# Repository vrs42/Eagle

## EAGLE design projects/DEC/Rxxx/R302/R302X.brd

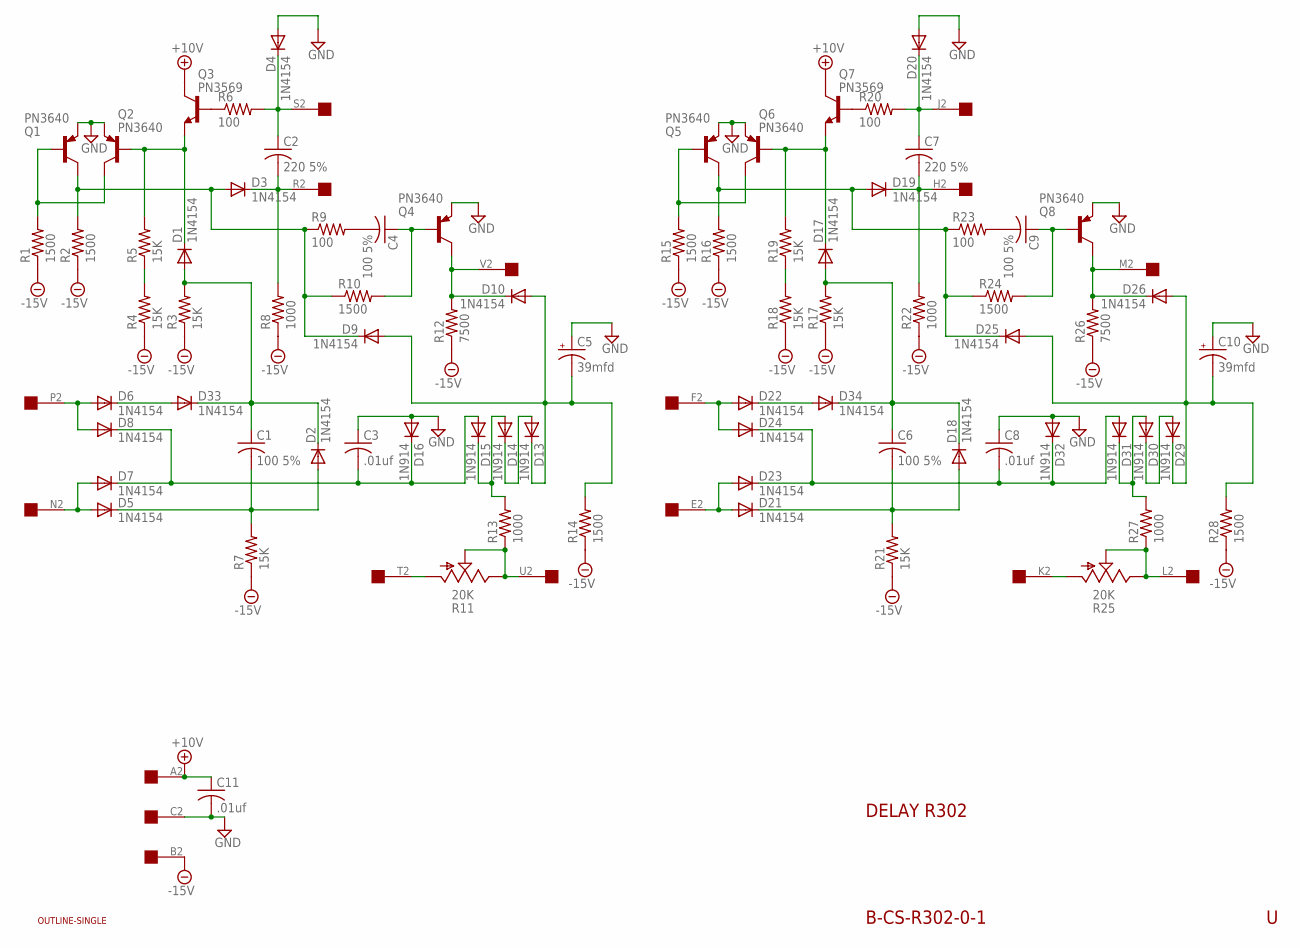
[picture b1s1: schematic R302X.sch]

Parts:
C1, C4, C6, C9: 100 5%; C050-025X075
C2, C7: 220 5%; C050-025X075
C3, C8, C11: .01uf; C050-025X075
C5, C10: 39mfd; E15-5
D1, D2, D3, D4, D5, D6, D7, D8, D9, D10, D17, D18, D19, D20, D21, D22, D23, D24, D25, D26, D33, D34: 1N4154; DO35-10
D13, D14, D15, D16, D29, D30, D31, D32: 1N914; DO35-10
Q1, Q2, Q4, Q5, Q6, Q8: PN3640; TO39
Q3, Q7: PN3569; TO39
R1, R2, R10, R14, R15, R16, R24, R28: 1500; 0207/10
R3, R4, R5, R7, R17, R18, R19, R21: 15K; 0207/10
R6, R9, R20, R23: 100; 0207/10
R8, R13, R22, R27: 1000; 0207/10
R11, R25: 20K; SP19L
R12, R26: 7500; 0207/10
U$1: OUTLINE-SINGLE; SINGLE
U$2: EDGE-1; EDGE-CON1

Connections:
+10V: C11.1, Q3.3 (C), Q7.3 (C), U$2.A2
-15V: R1.1, R2.1, R3.1, R4.1, R7.1, R8.1, R12.1, R14.1, R15.1, R16.1, R17.1, R18.1, R21.1, R22.1, R26.1, R28.1, U$2.B2
GND: C3.1, C5.+, C8.1, C10.+, C11.2, D4.A, D16.A, D20.A, D32.A, Q1.1 (E), Q2.1 (E), Q4.1 (E), Q5.1 (E), Q6.1 (E), Q8.1 (E), U$2.C2
unnamed: C2.1, D4.C, R6.2, U$2.S2
unnamed: C2.2, D3.C, R8.2, U$2.R2
unnamed: D1.C, Q2.2 (B), Q3.1 (E), R5.2
unnamed: R4.2, R5.1
unnamed: D22.A, D24.A, U$2.F2
unnamed: Q3.2 (B), R6.1
unnamed: R11.E, R11.S, R13.1, U$2.U2
unnamed: C1.1, D1.A, D2.C, D33.C, R3.2
unnamed: D5.A, D7.A, U$2.N2
unnamed: R11.A, U$2.T2
unnamed: D6.C, D33.A
unnamed: D6.A, D8.A, U$2.P2
unnamed: C1.2, D2.A, D5.C, R7.2
unnamed: C3.2, D7.C, D8.C, D15.A, D16.C
unnamed: C4.2, R9.2
unnamed: Q1.2 (B), Q2.3 (C), R1.2
unnamed: C4.1, Q4.2 (B), R10.2
unnamed: D3.A, D9.C, Q1.3 (C), R2.2, R9.1, R10.1
unnamed: D10.C, Q4.3 (C), R12.2, U$2.V2
unnamed: Q5.2 (B), Q6.3 (C), R15.2
unnamed: D13.A, D14.C
unnamed: D19.A, D25.C, Q5.3 (C), R16.2, R23.1, R24.1
unnamed: C5.-, D9.A, D10.A, D13.C, R14.2
unnamed: D17.C, Q6.2 (B), Q7.1 (E), R19.2
unnamed: Q7.2 (B), R20.1
unnamed: C7.1, D20.C, R20.2, U$2.J2
unnamed: C7.2, D19.C, R22.2, U$2.H2
unnamed: R18.2, R19.1
unnamed: D22.C, D34.A
unnamed: C6.1, D17.A, D18.C, D34.C, R17.2
unnamed: C6.2, D18.A, D21.C, R21.2
unnamed: D21.A, D23.A, U$2.E2
unnamed: C8.2, D23.C, D24.C, D31.A, D32.C
unnamed: C9.2, R23.2
unnamed: C9.1, Q8.2 (B), R24.2
unnamed: D26.C, Q8.3 (C), R26.2, U$2.M2
unnamed: D29.A, D30.C
unnamed: C10.-, D25.A, D26.A, D29.C, R28.2
unnamed: R25.E, R25.S, R27.1, U$2.L2
unnamed: R25.A, U$2.K2
unnamed: D14.A, D15.C, R13.2
unnamed: D30.A, D31.C, R27.2

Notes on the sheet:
DELAY R302
B-CS-R302-0-1

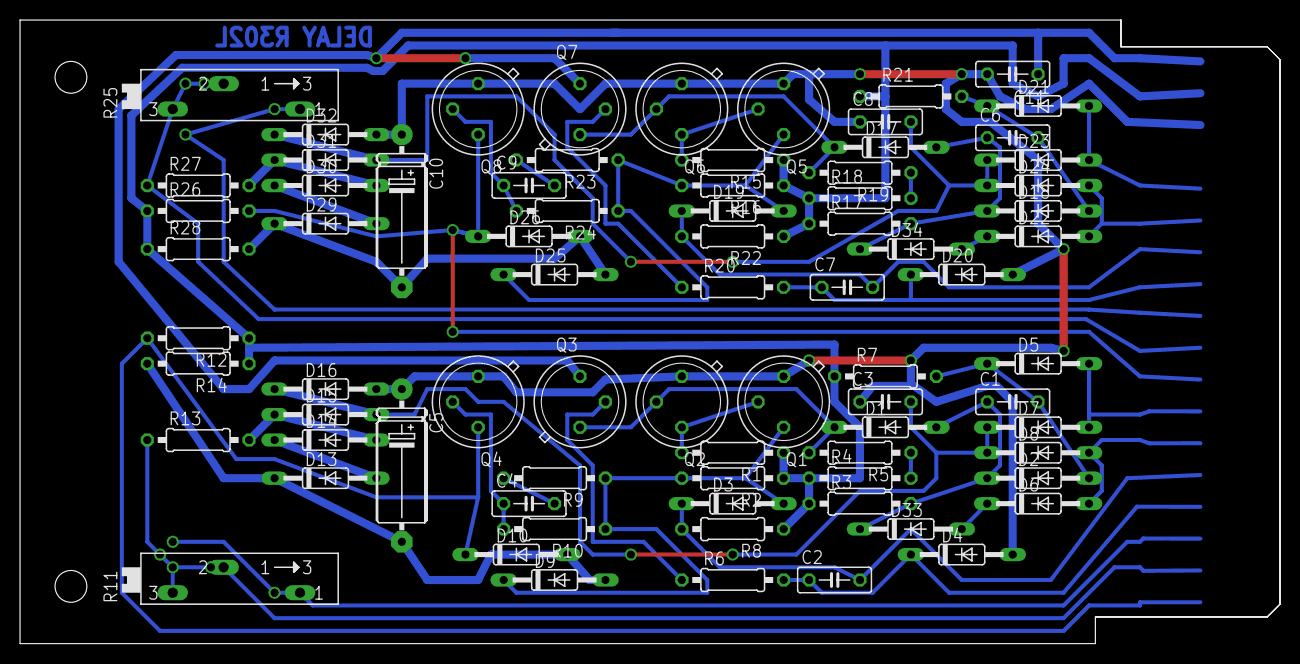
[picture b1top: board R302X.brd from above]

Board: 2 copper layers, 125.7 x 62.2 mm, 79 parts (0 on the bottom side), 45 nets.

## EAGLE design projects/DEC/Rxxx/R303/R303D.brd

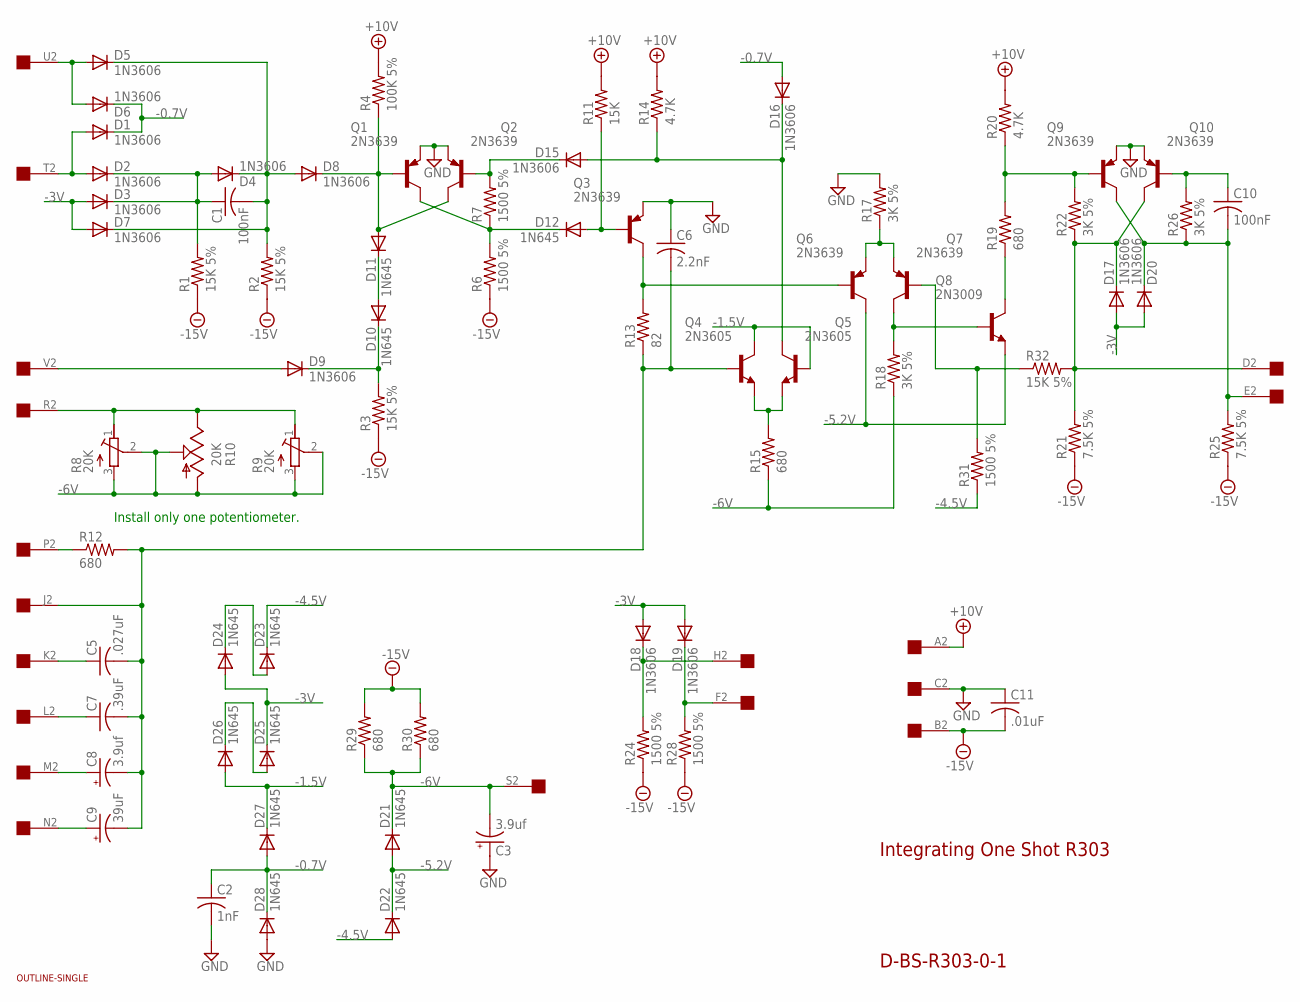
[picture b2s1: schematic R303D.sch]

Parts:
C1, C10: 100nF; C075-032X103
C2: 1nF; C050-025X075
C3, C8: 3.9uf; E12-4
C5: .027uF; C225-062X268
C6: 2.2nF; C050-025X075
C7: .39uF; C325-137X374
C9: 39uF; E15-5
C11: .01uF; C075-032X103
D1, D2, D3, D4, D5, D6, D7, D8, D9, D15, D16, D17, D18, D19, D20: 1N3606; DO35-10
D10, D11, D12, D21, D22, D23, D24, D25, D26, D27, D28: 1N645; DO35-10
Q1, Q2, Q3, Q6, Q7, Q9, Q10: 2N3639; TO39
Q4, Q5: 2N3605; TO5
Q8: 2N3009; TO5
R1, R2, R3, R32: 15K 5%; 0207/10
R4: 100K 5%; 0207/10
R6, R7, R24, R28, R31: 1500 5%; 0207/10
R8: 20K; RTRIM43P
R9: 20K; 3006Y
R10: 20K; B25P
R11: 15K; 0207/10
R12, R15, R19, R29, R30: 680; 0207/10
R13: 82; 0207/10
R14, R20: 4.7K; 0207/10
R17, R18, R22, R26: 3K 5%; 0207/10
R21, R25: 7.5K 5%; 0207/10
U$1: OUTLINE-SINGLE; SINGLE
U$2: EDGE-1; EDGE-CON1

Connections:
+10V: R4.2, R11.2, R14.2, R20.2, U$2.A2
-0.7V: C2.1, D1.C, D6.C, D16.A, D27.A, D28.C
-1.5V: D26.A, D27.C, Q4.3 (C), Q5.2 (B)
-3V: D3.A, D7.A, D17.A, D18.A, D19.A, D20.A, D24.A, D25.C
-4.5V: D22.A, D23.C, R31.1
-5.2V: D21.A, D22.C, Q6.3 (C), Q8.1 (E)
-6V: C3.-, D21.C, R8.2 (S), R8.3 (A), R9.2 (S), R9.3 (E), R10.A, R10.S, R15.1, R18.1, R29.1, R30.1, U$2.S2
-15V: C11.2, R1.1, R2.1, R3.1, R6.1, R21.1, R24.1, R25.1, R28.1, R29.2, R30.2, U$2.B2
GND: C2.2, C3.+, C6.1, C11.1, D28.A, Q1.1 (E), Q2.1 (E), Q3.1 (E), Q9.1 (E), Q10.1 (E), R17.2, U$2.C2
unnamed: D1.A, D2.A, U$2.T2
unnamed: C1.1, D2.C, D3.C, D4.A, R1.2
unnamed: D5.A, D6.A, U$2.U2
unnamed: C1.2, D4.C, D5.C, D7.C, D8.A, R2.2
unnamed: D8.C, D11.A, Q1.2 (B), Q2.3 (C), R4.1
unnamed: D12.C, Q1.3 (C), R6.2, R7.1
unnamed: D15.C, Q2.2 (B), R7.2
unnamed: D9.C, D10.C, R3.2
unnamed: D10.A, D11.C
unnamed: D9.A, U$2.V2
unnamed: D12.A, Q3.2 (B), R11.1
unnamed: R8.1 (E), R9.1 (A), R10.E, U$2.R2
unnamed: C9.+, U$2.N2
unnamed: C8.+, U$2.M2
unnamed: C7.1, U$2.L2
unnamed: C5.1, U$2.K2
unnamed: C5.2, C6.2, C7.2, C8.-, C9.-, Q4.2 (B), R12.2, R13.1, U$2.J2
unnamed: D25.A, D26.C
unnamed: D23.A, D24.C
unnamed: Q3.3 (C), Q6.2 (B), R13.2
unnamed: R12.1, U$2.P2
unnamed: Q6.1 (E), Q7.1 (E), R17.1
unnamed: Q4.1 (E), Q5.1 (E), R15.2
unnamed: Q7.3 (C), Q8.2 (B), R18.2
unnamed: D15.A, D16.C, Q5.3 (C), R14.1
unnamed: Q9.2 (B), R19.2, R20.1, R22.2
unnamed: Q8.3 (C), R19.1
unnamed: D17.C, Q10.3 (C), R21.2, R22.1, R32.2, U$2.D2
unnamed: C10.2, D20.C, Q9.3 (C), R25.2, R26.1, U$2.E2
unnamed: C10.1, Q10.2 (B), R26.2
unnamed: D18.C, R24.2, U$2.H2
unnamed: D19.C, R28.2, U$2.F2
unnamed: Q7.2 (B), R31.2, R32.1

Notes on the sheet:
Install only one potentiometer.
Integrating One Shot R303
D-BS-R303-0-1

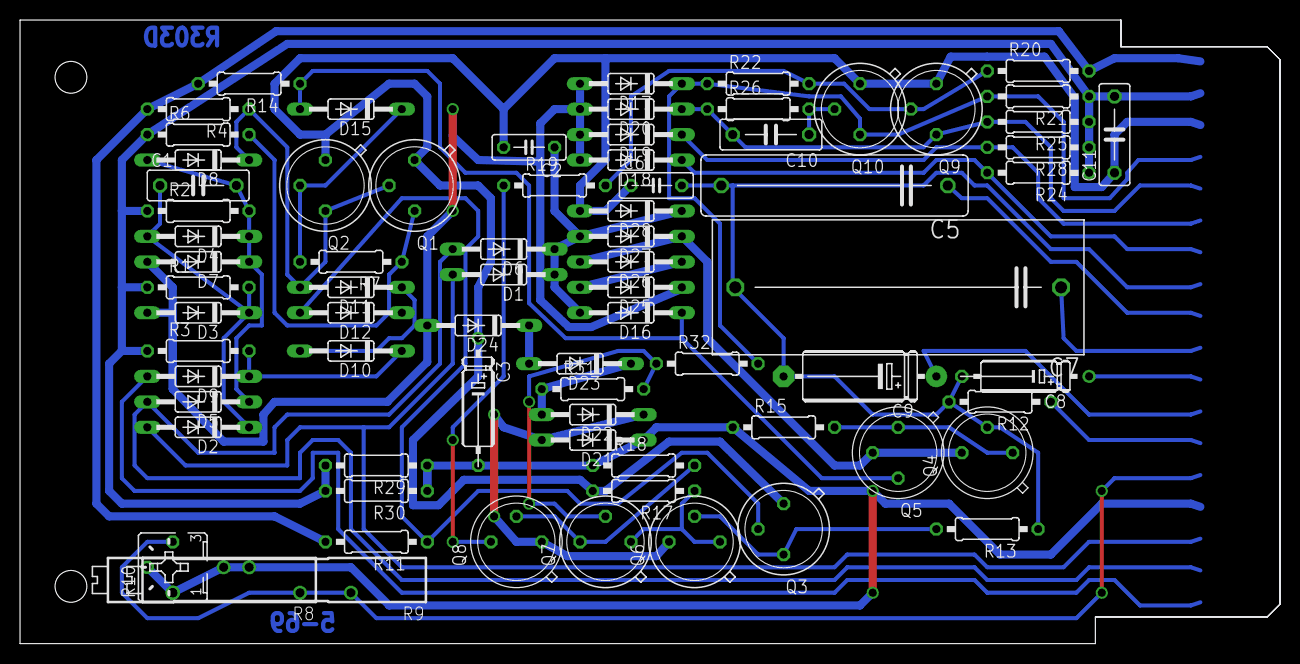
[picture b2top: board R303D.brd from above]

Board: 2 copper layers, 125.7 x 62.2 mm, 76 parts (0 on the bottom side), 42 nets.

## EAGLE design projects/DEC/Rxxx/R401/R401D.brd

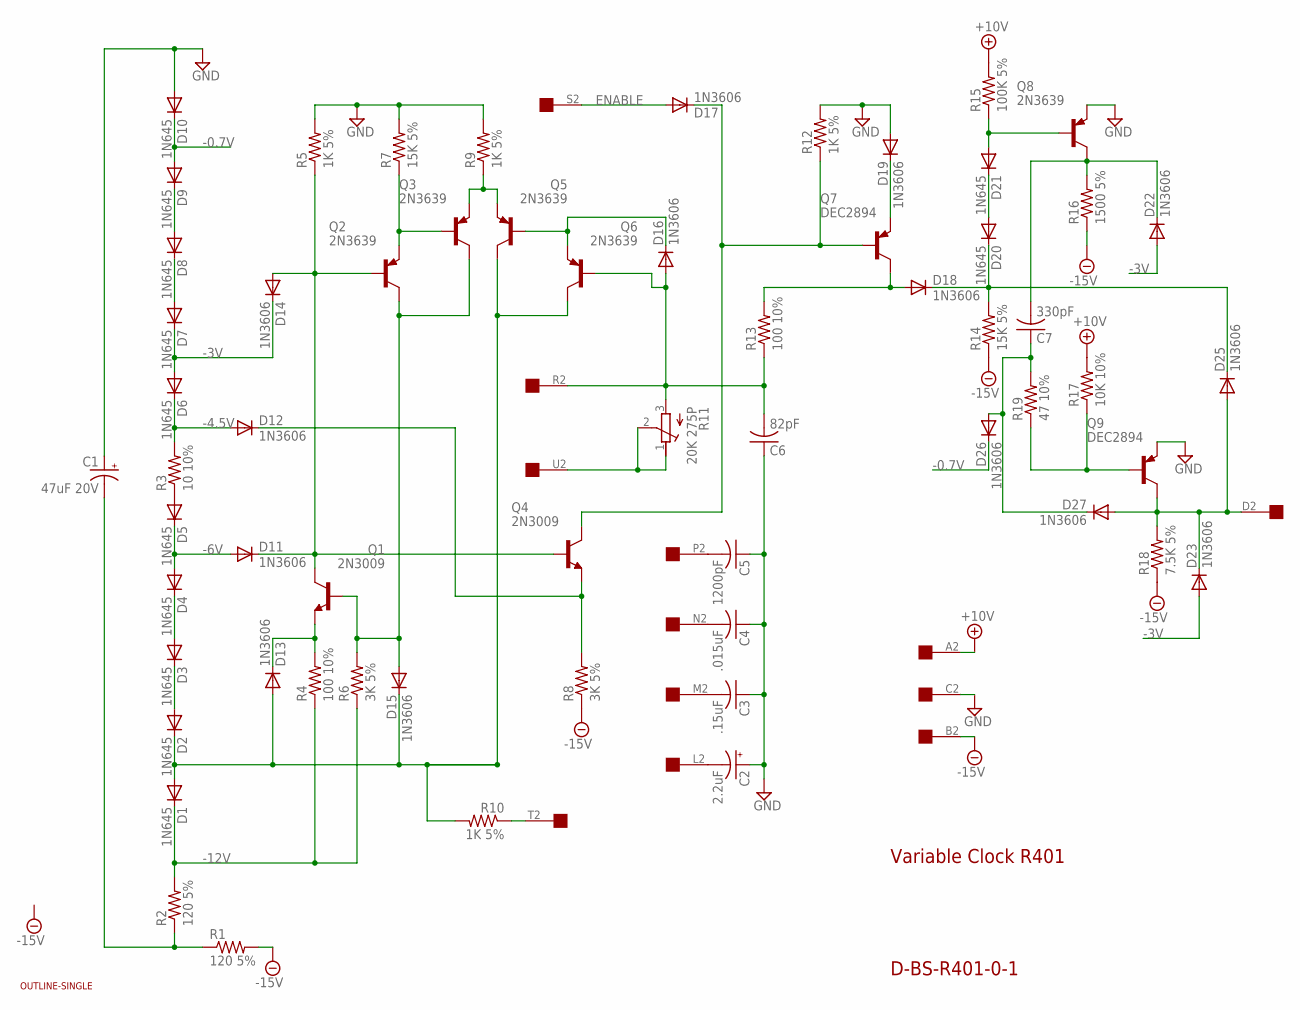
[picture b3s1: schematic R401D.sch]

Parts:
C1: 47uF 20V; E22-6
C2: 2.2uF; E12-4
C3: .15uF; C275-093X316
C4: .015uF; C150-054X183
C5: 1200pF; C102-043X133
C6: 82pF; C075-032X103
C7: 330pF; C075-032X103
D1, D2, D3, D4, D5, D6, D7, D8, D9, D10, D20, D21: 1N645; DO35-10
D11, D12, D13, D14, D15, D16, D17, D18, D19, D22, D23, D25, D26, D27: 1N3606; DO35-10
Q1, Q4: 2N3009; TO5
Q2, Q3, Q5, Q6, Q8: 2N3639; TO39
Q7, Q9: DEC2894; TO39
R1, R2: 120 5%; 0207/10
R3: 10 10%; 0207/10
R4, R13: 100 10%; 0207/10
R5, R9, R10, R12: 1K 5%; 0207/10
R6, R8: 3K 5%; 0207/10
R7, R14: 15K 5%; 0207/10
R11: 20K 275P; 3006Y
R15: 100K 5%; 0207/10
R16: 1500 5%; 0207/10
R17: 10K 10%; 0207/10
R18: 7.5K 5%; 0207/10
R19: 47 10%; 0207/10
U$1: OUTLINE-SINGLE; SINGLE
U$2: EDGE-1; EDGE-CON1

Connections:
+10V: R15.2, R17.2, U$2.A2
-0.7V: D9.A, D10.C, D26.C
-3V: D6.A, D7.C, D14.C, D22.A, D23.A
-4.5V: D6.C, D12.A, R3.2
-6V: D4.A, D5.C, D11.A
-12V: D1.C, R2.2, R4.1, R6.1
-15V: R1.2, R8.1, R14.1, R16.1, R18.1, U$2.B2
ENABLE: D17.A, U$2.S2
GND: C1.+, C2.+, C3.1, C4.1, C5.1, C6.1, D10.A, D19.A, Q8.1 (E), Q9.1 (E), R5.2, R7.2, R9.2, R12.2, U$2.C2
unnamed: C1.-, R1.1, R2.1
unnamed: D5.A, R3.1
unnamed: D11.C, D14.A, Q1.3 (C), Q2.2 (B), Q4.2 (B), R5.1
unnamed: D8.A, D9.C
unnamed: D7.A, D8.C
unnamed: D13.C, Q1.1 (E), R4.2
unnamed: D15.A, Q1.2 (B), Q2.3 (C), Q3.3 (C), R6.2
unnamed: D1.A, D2.C, D13.A, D15.C, Q5.3 (C), Q6.3 (C), R10.2
unnamed: D2.A, D3.C
unnamed: D3.A, D4.C
unnamed: Q2.1 (E), Q3.2 (B), R7.1
unnamed: Q3.1 (E), Q5.1 (E), R9.1
unnamed: D12.C, Q4.1 (E), R8.2
unnamed: D16.C, Q5.2 (B), Q6.1 (E)
unnamed: C6.2, D16.A, Q6.2 (B), R11.3 (E), R13.1, U$2.R2
unnamed: R11.1 (A), R11.2 (S), U$2.U2
unnamed: D17.C, Q4.3 (C), Q7.2 (B), R12.1
unnamed: D19.C, Q7.1 (E)
unnamed: D18.A, Q7.3 (C), R13.2
unnamed: C4.2, U$2.N2
unnamed: D23.C, D25.A, D27.A, Q9.3 (C), R18.2, U$2.D2
unnamed: C3.2, U$2.M2
unnamed: C2.-, U$2.L2
unnamed: C5.2, U$2.P2
unnamed: D21.A, Q8.2 (B), R15.1
unnamed: D20.A, D21.C
unnamed: C7.2, D22.C, Q8.3 (C), R16.2
unnamed: D18.C, D20.C, D25.C, R14.2
unnamed: Q9.2 (B), R17.1, R19.1
unnamed: C7.1, D26.A, D27.C, R19.2
unnamed: R10.1, U$2.T2

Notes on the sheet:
Variable Clock R401
D-BS-R401-0-1

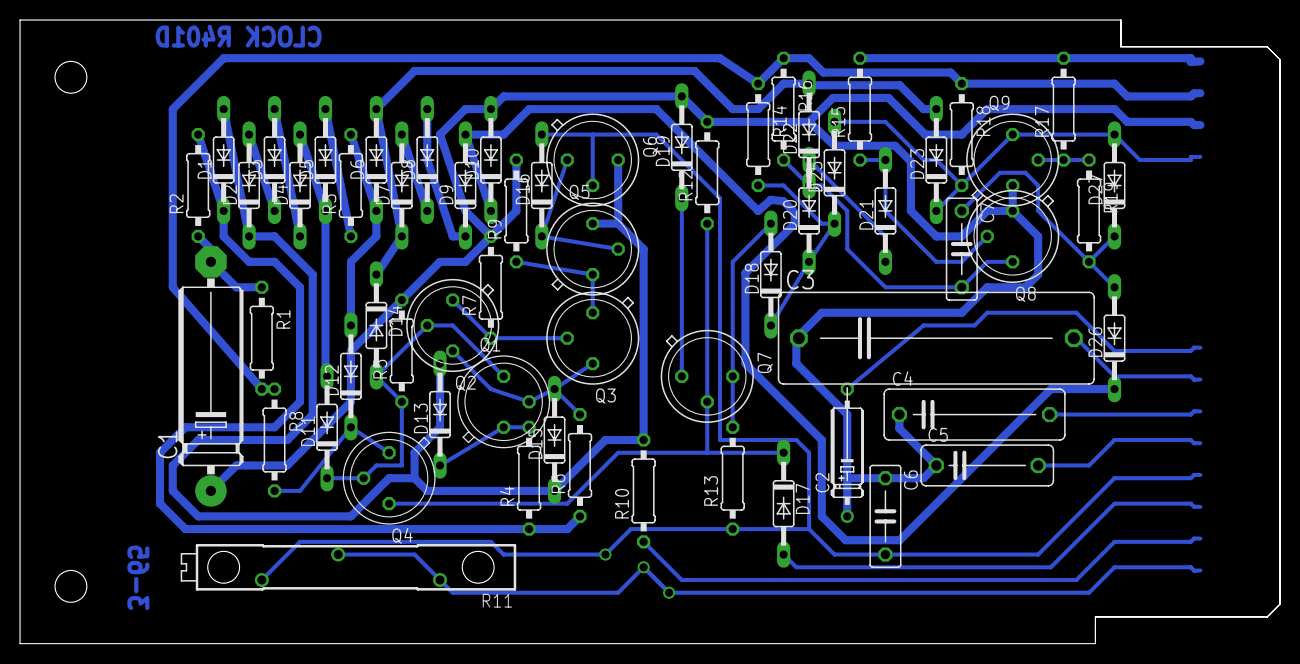
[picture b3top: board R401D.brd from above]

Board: 2 copper layers, 125.7 x 62.2 mm, 63 parts (0 on the bottom side), 40 nets.
